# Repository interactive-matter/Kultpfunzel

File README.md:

Kultpfunzel
===========

The Customisable Smart Torch
----------------------------

The Kultpfunzel is an Arduino-powered LED torch,
designed to retrofit into a Swiss Army torch enclosure.

The board is Arduino compatible. 

Get the full documentation and show off your hacks at http://kultpfunzel.ch/die-kultpfunzel

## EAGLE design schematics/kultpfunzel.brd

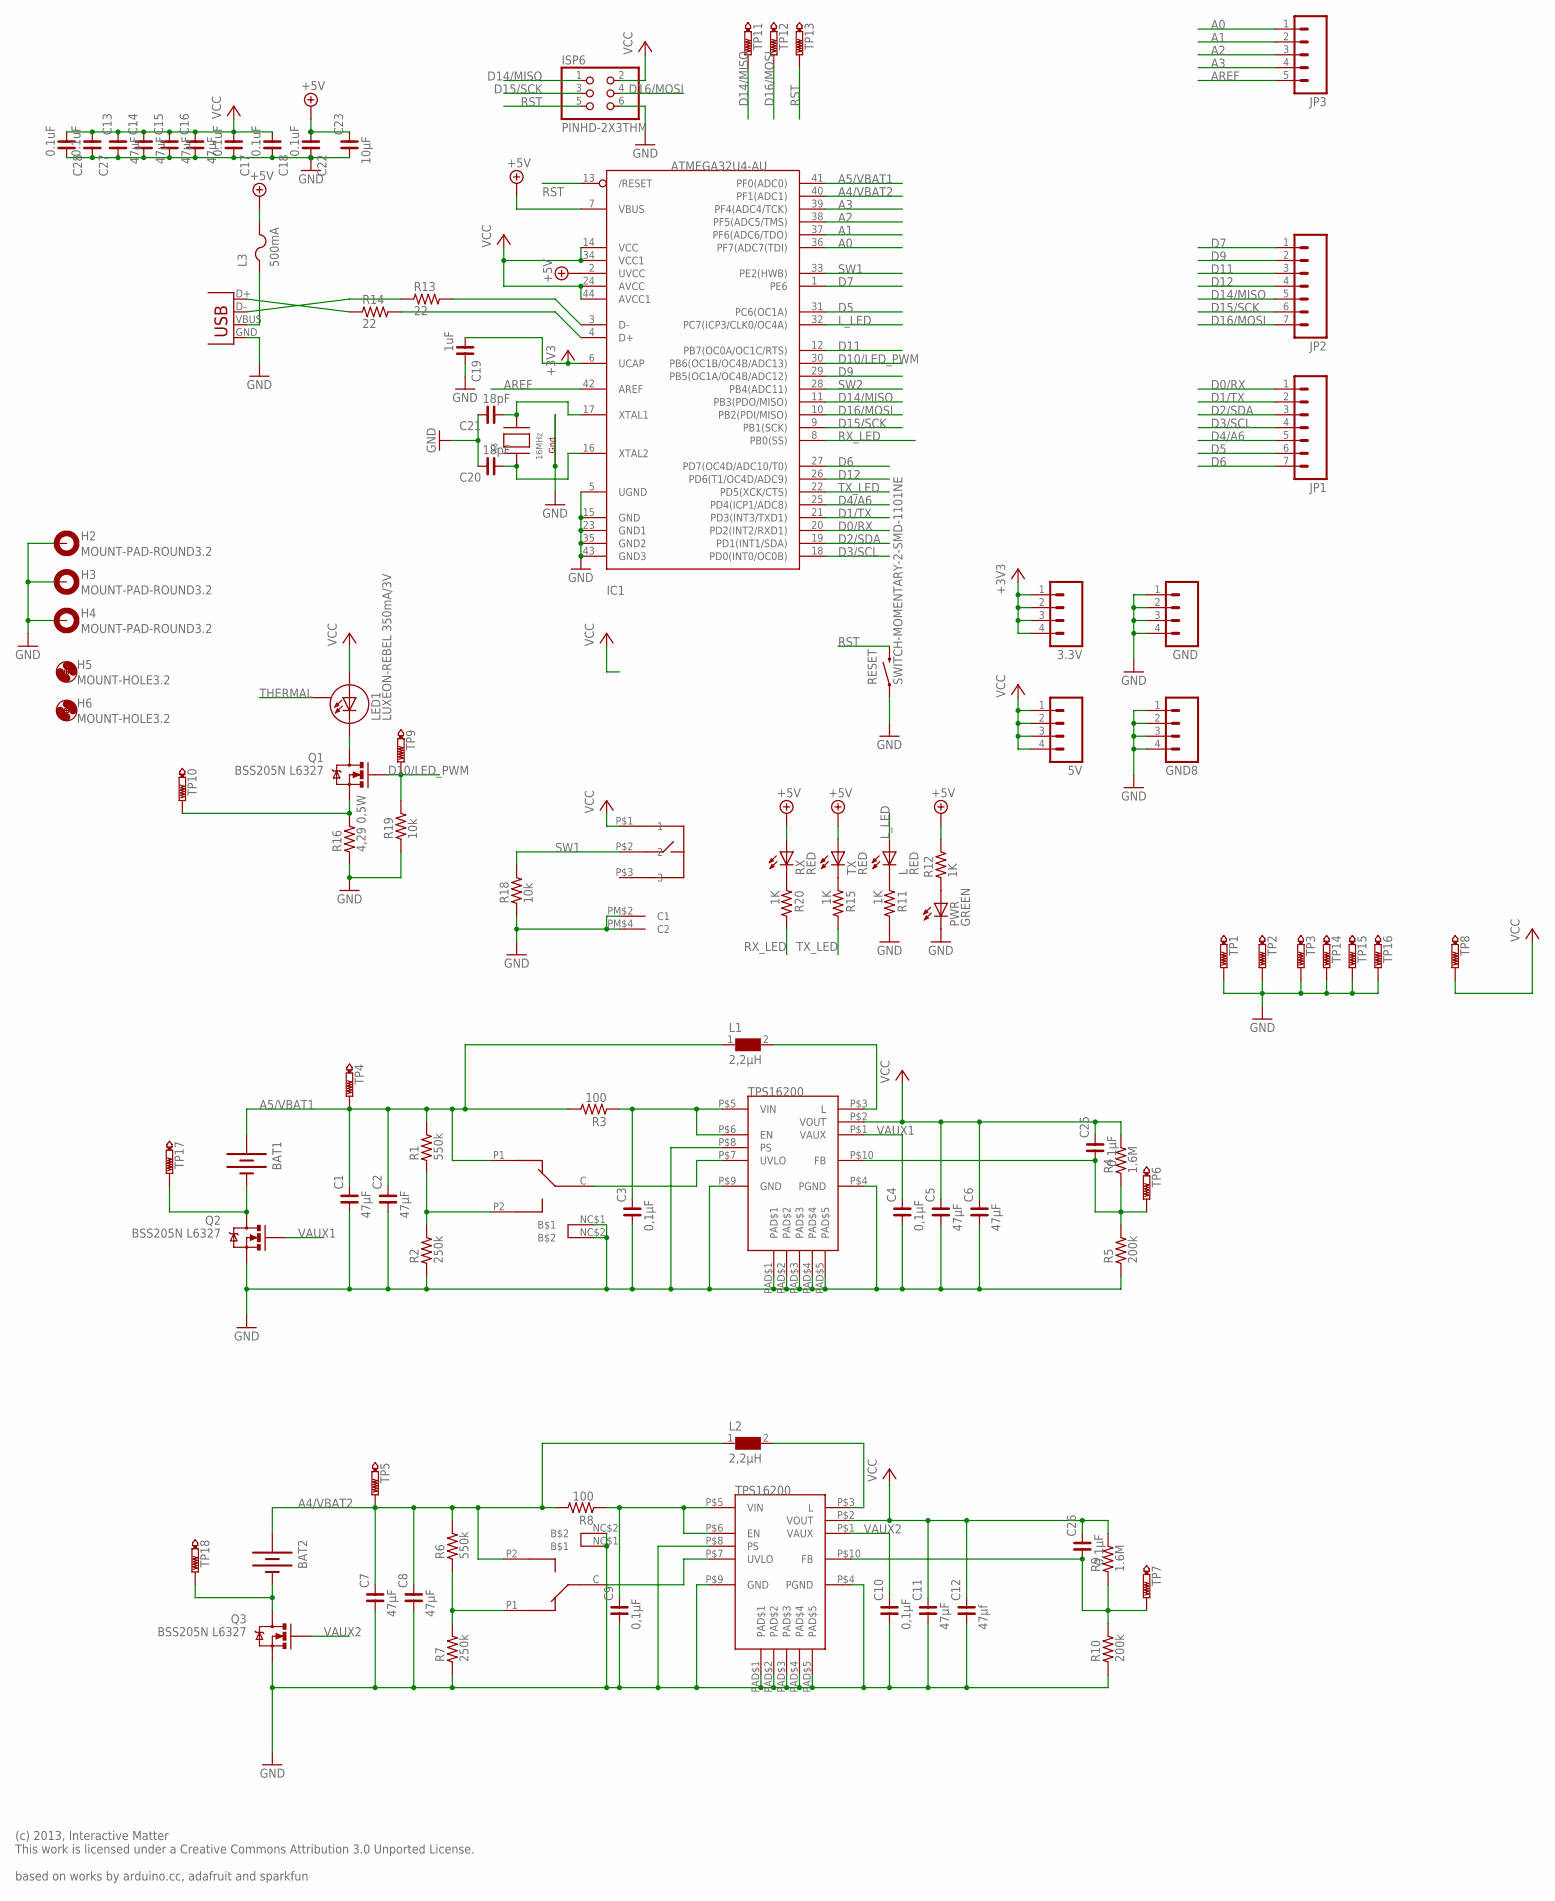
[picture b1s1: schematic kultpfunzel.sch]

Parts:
3.3V, 5V: M04PTH; 1X04
BAT1, BAT2: BATTERYAA; BATTERY-AA
C1, C2, C7, C8, C13, C14, C15, C16: 47µF; C1206
C3, C4, C9, C10: 0,1µF; C0402
C5, C6, C11: 47µF; C0805
C12: 47µf; C0805
C17, C18, C27, C28: 0.1uF; C0402
C19: 1uF; C0603
C20, C21: 18pF; C0402
C22: 0.1uF; C0603
C23: 10µF; C1206
C25, C26: 0,1µF; C0603
GND, GND8: M04PTH; 1X04
H2, H3, H4: MOUNT-PAD-ROUND3.2; 3,2-PAD
H5, H6: MOUNT-HOLE3.2; 3,2
IC1: ATMEGA32U4-AU; TQFP44
IC2, IC3: TPS61200DRCT; 10SON
ISP6: PINHD-2X3THM; ISP6
JP1, JP2: M07; 1X07
JP3: M05PTH; 1X05
L: RED; CHIPLED_0603
L1, L2: 2,2µH; WE-PD2_M/MS
L3: 500mA; R1206
LED1: LUXEON-REBEL 350mA/3V; LUXEON-REBEL
PWR: GREEN; CHIPLED_0603
Q1, Q2, Q3: BSS205N L6327; SOT23-3
R1, R6: 550k; R0603
R2, R7: 250k; R0603
R3, R8: 100; R0603
R4, R9: 1.6M; R0603
R5, R10: 200k; R0603
R11, R12, R15, R20: 1K; R0603
R13, R14: 22; R0603
R16: 4,29 0,5W; R1210
R18, R19: 10k; R0603
RESET: SWITCH-MOMENTARY-2-SMD-1101NE; TACTILE-SWITCH-1101NE
RX: RED; CHIPLED_0603
SW: TL4105AF
SW1, SW2: SMDSWITCHAYZ0102; SMDSWITCH
TP1, TP2, TP3, TP4, TP5, TP6, TP7, TP8, TP9, TP10, TP11, TP12, TP13, TP14, TP15, TP16, TP17, TP18: PTR1B1,27; B1,27
TX: RED; CHIPLED_0603
USB: USB; USB-MINIB-VERT
X3: 16MHz; NX3225

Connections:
+3V3: 3.3V.1, 3.3V.2, 3.3V.3, 3.3V.4, C19.1, IC1.6 (UCAP)
+5V: C22.1, C23.2, IC1.2 (UVCC), IC1.7 (VBUS), L3.2, R12.2, RX.A, TX.A
A0: IC1.36 (PF7(ADC7(TDI)), JP3.1
A1: IC1.37 (PF6(ADC6/TDO)), JP3.2
A2: IC1.38 (PF5(ADC5/TMS)), JP3.3
A3: IC1.39 (PF4(ADC4/TCK)), JP3.4
A4/VBAT2: BAT2.PWR@1 (+), C7.2, C8.2, IC1.40 (PF1(ADC1)), L2.1, R6.2, R8.2, SW1.P2, TP5.TP
A5/VBAT1: BAT1.PWR@1 (+), C1.2, C2.2, IC1.41 (PF0(ADC0)), L1.1, R1.2, R3.2, SW2.P1, TP4.TP
AREF: IC1.42 (AREF), JP3.5
D0/RX: IC1.20 (PD2(INT2/RXD1)), JP1.1
D1/TX: IC1.21 (PD3(INT3/TXD1)), JP1.2
D2/SDA: IC1.19 (PD1(INT1/SDA)), JP1.3
D3/SCL: IC1.18 (PD0(INT0/OC0B)), JP1.4
D4/A6: IC1.25 (PD4(ICP1/ADC8)), JP1.5
D5: IC1.31 (PC6(OC1A)), JP1.6
D6: IC1.27 (PD7(OC4D/ADC10/T0)), JP1.7
D7: IC1.1 (PE6), JP2.1
D9: IC1.29 (PB5(OC1A/OC4B/ADC12)), JP2.2
D10/LED_PWM: IC1.30 (PB6(OC1B/OC4B/ADC13)), Q1.1 (G), R19.2, TP9.TP
D11: IC1.12 (PB7(OC0A/OC1C/RTS)), JP2.3
D12: IC1.26 (PD6(T1/OC4D/ADC9)), JP2.4
D14/MISO: IC1.11 (PB3(PDO/MISO)), ISP6.1, JP2.5, TP11.TP
D15/SCK: IC1.9 (PB1(SCK)), ISP6.3, JP2.6
D16/MOSI: IC1.10 (PB2(PDI/MISO)), ISP6.4, JP2.7, TP12.TP
GND: C1.1, C2.1, C3.1, C4.1, C5.1, C6.1, C7.1, C8.1, C9.1, C10.1, C11.1, C12.1, C13.1, C14.1, C15.1, C16.1, C17.2, C18.2, C19.2, C20.2, C21.2, C22.2, C23.1, C27.2, C28.2, GND.1, GND.2, GND.3, GND.4, GND8.1, GND8.2, GND8.3, GND8.4, H2.B3,2, H3.B3,2, H4.B3,2, IC1.5 (UGND), IC1.15 (GND), IC1.23 (GND1), IC1.35 (GND2), IC1.43 (GND3), IC2.P$4 (PGND), IC2.P$8 (PS), IC2.P$9 (GND), IC2.PAD$1, IC2.PAD$2, IC2.PAD$3, IC2.PAD$4, IC2.PAD$5, IC3.P$4 (PGND), IC3.P$8 (PS), IC3.P$9 (GND), IC3.PAD$1, IC3.PAD$2, IC3.PAD$3, IC3.PAD$4, IC3.PAD$5, ISP6.6, PWR.C, Q2.2 (S), Q3.2 (S), R2.1, R5.1, R7.1, R10.1, R11.2, R16.1, R18.1, R19.1, RESET.P$1 (1), SW.PM$2 (C1), SW.PM$4 (C2), SW1.NC$1, SW1.NC$2, SW2.NC$1, SW2.NC$2, TP1.TP, TP2.TP, TP3.TP, TP14.TP, TP15.TP, TP16.TP, USB.GND, X3.2 (G2), X3.4 (G1)
L_LED: IC1.32 (PC7(ICP3/CLK0/OC4A)), L.A
unnamed: PWR.A, R12.1
unnamed: R14.1, USB.D+
unnamed: IC1.3 (D-), R13.2
unnamed: IC1.4 (D+), R14.2
unnamed: R13.1, USB.D-
unnamed: LED1.CATHODE (C), Q1.3 (D)
unnamed: IC2.P$3 (L), L1.2
unnamed: C21.1, IC1.17 (XTAL1), X3.3 (X2)
unnamed: C20.1, IC1.16 (XTAL2), X3.1 (X1)
unnamed: L.C, R11.1
unnamed: R1.1, R2.2, SW2.P2
unnamed: IC2.P$7 (UVLO), SW2.C
unnamed: Q1.2 (S), R16.2, TP10.TP
unnamed: C25.1, IC2.P$10 (FB), R4.1, R5.2, TP6.TP
unnamed: BAT1.GND@1 (-), Q2.3 (D), TP17.TP
unnamed: BAT2.GND@1 (-), Q3.3 (D), TP18.TP
unnamed: R15.1, TX.C
unnamed: R20.1, RX.C
unnamed: R6.1, R7.2, SW1.P1
unnamed: IC3.P$7 (UVLO), SW1.C
unnamed: IC3.P$3 (L), L2.2
unnamed: C26.1, IC3.P$10 (FB), R9.1, R10.2, TP7.TP
RST: IC1.13 (/RESET), ISP6.5, RESET.P$2 (2), TP13.TP
RX_LED: IC1.8 (PB0(SS)), R20.2
SW1: IC1.33 (PE2(HWB)), R18.2, SW.P$2 (2)
SW2: IC1.28 (PB4(ADC11))
THERMAL: LED1.P$3 (S)
TX_LED: IC1.22 (PD5(XCK/CTS)), R15.2
VAUX1: C4.2, IC2.P$1 (VAUX), Q2.1 (G)
VAUX2: C10.2, IC3.P$1 (VAUX), Q3.1 (G)
VBUS: L3.1, USB.VBUS
VCC: 5V.1, 5V.2, 5V.3, 5V.4, C5.2, C6.2, C11.2, C12.2, C13.2, C14.2, C15.2, C16.2, C17.1, C18.1, C25.2, C26.2, C27.1, C28.1, IC1.14 (VCC), IC1.24 (AVCC), IC1.34 (VCC1), IC1.44 (AVCC1), IC2.P$2 (VOUT), IC3.P$2 (VOUT), ISP6.2, LED1.ANODE (A), R4.2, R9.2, SW.P$1 (1), TP8.TP
VI1: C3.2, IC2.P$5 (VIN), IC2.P$6 (EN), R3.1
VI2: C9.2, IC3.P$5 (VIN), IC3.P$6 (EN), R8.1

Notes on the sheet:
(c) 2013, Interactive Matter This work is licensed under a Creative Commons Attribution 3.0 Unported License. based on works by arduino.cc, adafruit and sparkfun

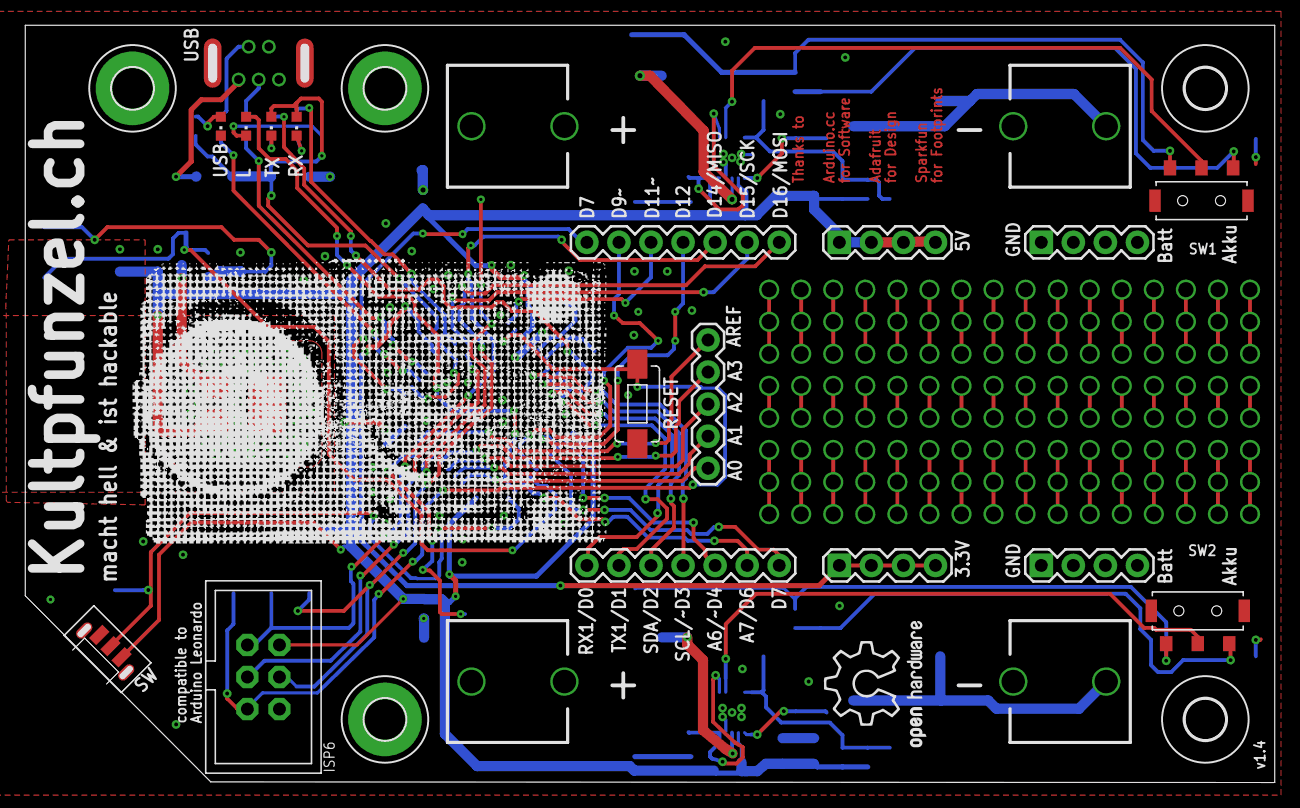
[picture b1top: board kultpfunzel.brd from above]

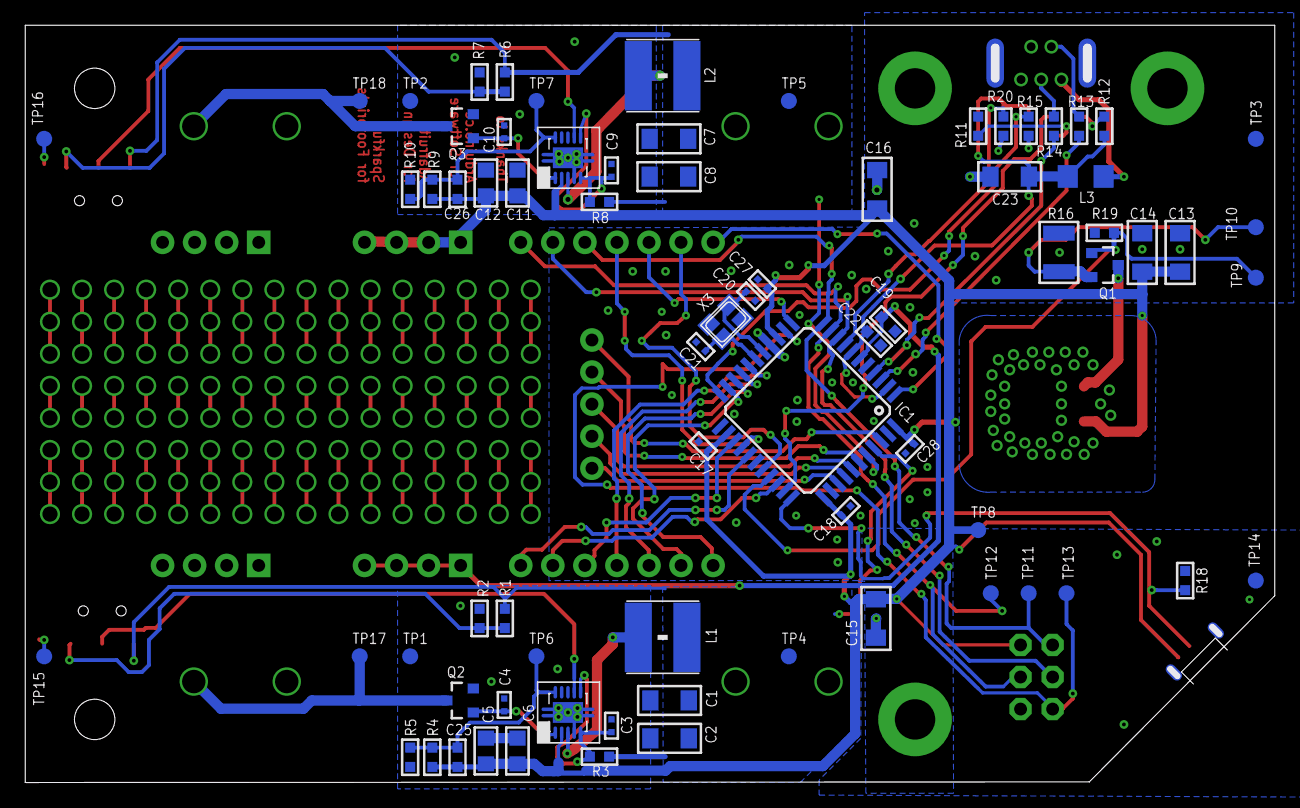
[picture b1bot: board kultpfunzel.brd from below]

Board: 2 copper layers, 99.0 x 60.0 mm, 101 parts (74 on the bottom side), 58 nets.

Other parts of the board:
U$1: LOGO
U$2: OSHW_LOGO_10MM

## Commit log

2013-09-30 the kultpfunzel code
2013-09-30 should be enough readme
2013-09-30 of course I got this wrong …
2013-09-30 yay, more typos
2013-09-30 better URL
2013-09-30 typo again & proof that the setup works
2013-10-04 adding the schematics
2014-02-05 More examples
2014-02-05 another example
2014-02-05 improved sketch
2014-02-05 bugfix: pinMetro without boolean argument
